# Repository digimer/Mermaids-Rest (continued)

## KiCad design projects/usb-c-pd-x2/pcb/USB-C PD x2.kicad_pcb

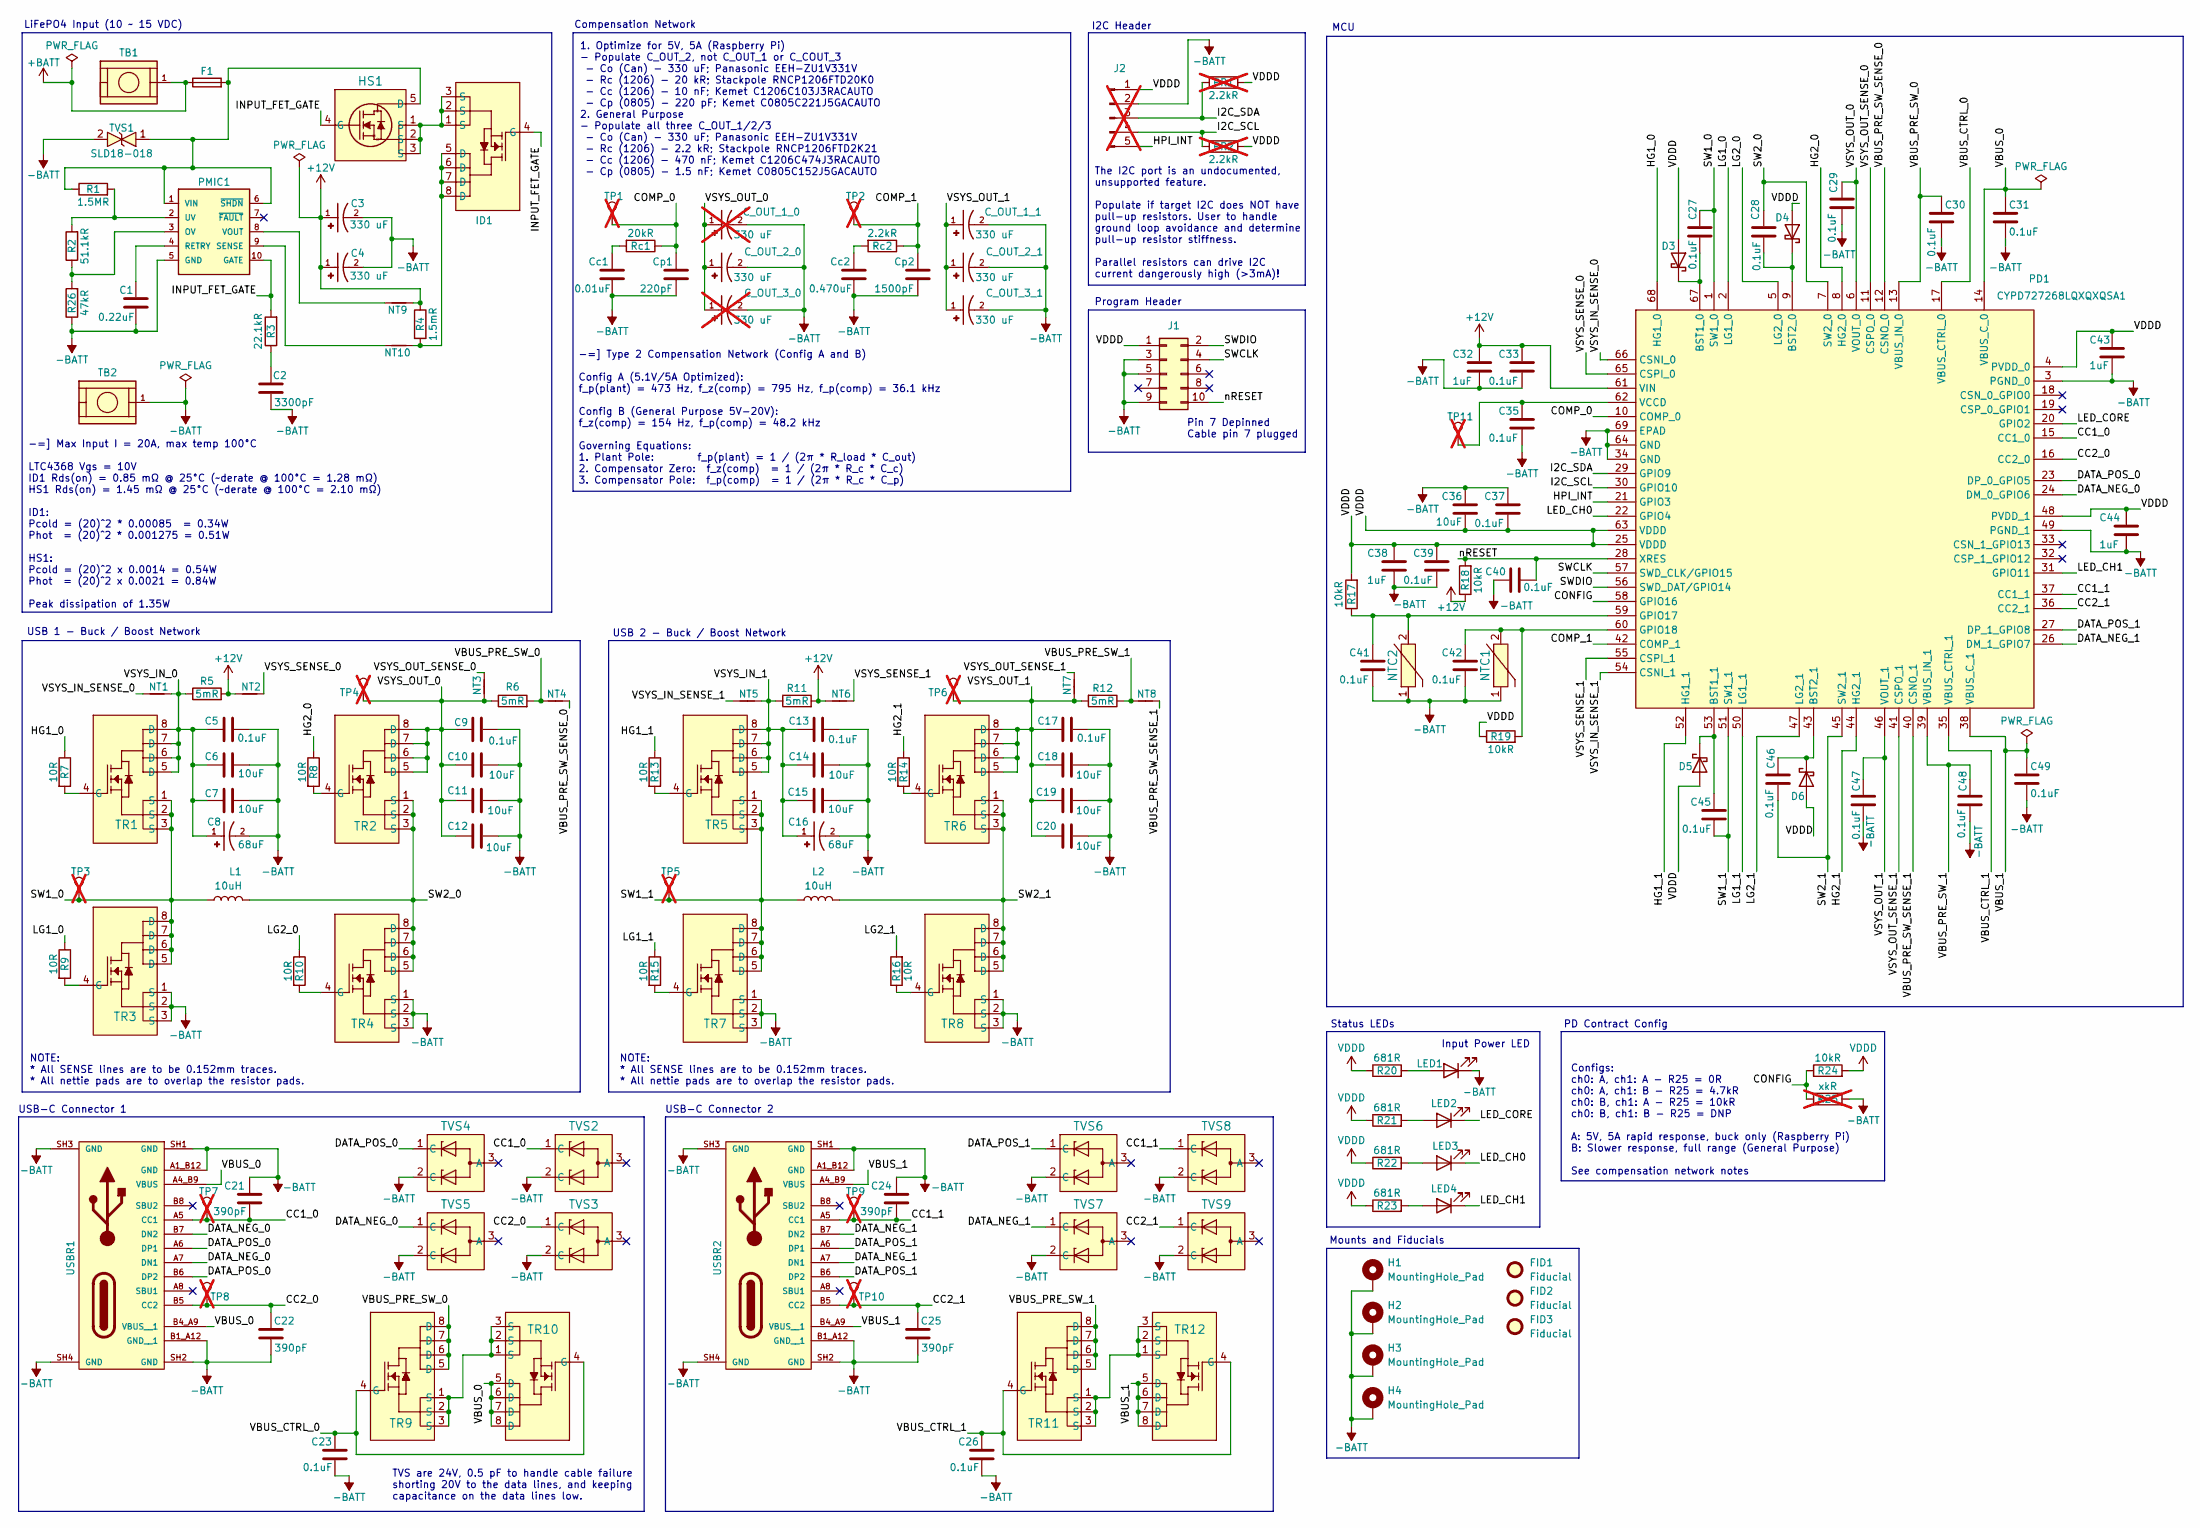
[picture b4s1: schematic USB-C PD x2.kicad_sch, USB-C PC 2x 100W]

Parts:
C1: 0.22uF; Kyocera AVX 08051A0R8CAT2A; Part Kyocera 08055C224J4Z2A
C2: 3300pF; C_0805_2012Metric; Part Kyocera KAM21BR71H332JT
C3, C4: 330 uF; Panasonic EEH-ZU; Part Panasonic EEH-ZU1V331V
C5, C9, C13, C17, C23, C26, C27, C28, C29, C30, C31, C33, C35, C37, C39, C40, C41, C42, C45, C46, C47, C48, C49: 0.1uF; Kyocera AVX 08051A0R8CAT2A; Part Kyocera 08051C104K4Z2A
C6, C7, C10, C11, C12, C14, C15, C18, C19, C20, C36: 10uF; TDK CGA5; Part TDK CGA5L1X7R1H106K160AE
C8, C16: 68uF; CP_Elec_8x10; Part Nichicon GXC1H680MCW1GS
C21, C22, C24, C25: 390pF; Yageo AC0805; Part Yageo AC0805JRNPO9BN391
C32, C38, C43, C44: 1uF; Kyocera AVX 08051A0R8CAT2A; Part Kyocera 08051C105K4Z2A
C_OUT_1_0, C_OUT_3_0: 330 uF; Panasonic EEH-ZU; Part Panasonic EEH-ZU1V331V; not fitted
C_OUT_1_1, C_OUT_2_0, C_OUT_2_1, C_OUT_3_1: 330 uF; Panasonic EEH-ZU; Part Panasonic EEH-ZU1V331V
Cc1: 0.01uF; C_1206_3216Metric; Part Kemet C1206C103J3RACAUTO
Cc2: 0.470uF; C_1206_3216Metric; Part Kemet C1206C474J3RACAUTO
Cp1: 220pF; C_0805_2012Metric; Part Kemet C0805C221J5GACAUTO
Cp2: 1500pF; C_0805_2012Metric; Part Kemet C0805C152J5GACAUTO
D3, D4, D5, D6: PMEG40T10ERX; Nexperia PMEG40; Part Nexperia PMEG40T10ERX
F1: Fuse; Littelfuse 178.6165.0001; Part Littelfuse 178.6165.0001
FID1, FID2, FID3: Fiducial; Fiducial_1mm_Mask2mm
H1, H2, H3, H4: MountingHole_Pad; MountingHole_4mm_Pad_Via
HS1: PSMN1R4-40YLDX; Nexperia PSMN1R4; Part Nexperia PSMN1R4-40YLDX
ID1: IAUC120N04S6L008ATMA1; Infineon IAUC120N04S6L008ATMA1; Part Infineon IAUC120N04S6L008ATMA1
J1: Conn_02x05_Odd_Even; PinHeader_2x05_P1.27mm_Vertical; Part Sullins GRPB052VWVN-RC
J2: Conn_01x05_Pin; PinHeader_1x05_P2.54mm_Vertical; Part Amphenol 68001-416HLF; not fitted
L1, L2: 10uH; Codaca CSBL1809-100M; Part Codaca CSBL1809-100M
LED1, LED2, LED3, LED4: LED; ams OSRAM LS Q976.01; Part ams OSRAM LS Q976.01-N1Q2-1
NT1, NT2, NT3, NT4, NT5, NT6, NT7, NT8, NT9, NT10: NetTie_2; NetTie-2_SMD_Pad0.2mm
NTC1, NTC2: Vishay NTCS0805E3103FHT; Vishay NTCS0805E; Part Vishay NTCS0805E3103FHT
PD1: CYPD727268LQXQXQSA1; QFN-68-1EP_8x8mm_P0.4mm_EP5.2x5.2mm_ThermalVias; Part Infineon CYPD727268LQXQXQSA1
PMIC1: ADI LTC4368; Part ADI LTC4368IMS-1#PBF
PR1, PR2: 2.2kR; R_1206_3216Metric; Part Stackpole RNCP1206FTD2K21; not fitted
R1: 1.5MR; Wurth WRIS-RSKS; Part Wurth 560112132040
R2: 51.1kR; R_1206_3216Metric; Part Stackpole RNCP1206FTD51K1
R3: 22.1kR; R_1206_3216Metric; Part Stackpole RNCP1206FTD22K1
R4: 1.5mR; Vishay WSLF2512; Part Vishay WSLF25121L500FEA
R5, R6, R11, R12: 5mR; Vishay WSLP; Part Vishay WSLP25125L000FEA
R7, R8, R9, R10, R13, R14, R15, R16: 10R; Stackpole RMCA0805; Part Stackpole RNCP0805FTD10R0
R17, R18, R19: 10kR; R_1206_3216Metric; Part Stackpole RNCP1206FTD10K0
R20, R21, R22, R23: 681R; Stackpole RMCA0805; Part Stackpole RNCP0805FTD681R
R24: 10kR; Stackpole_RNCP1206; Part Stackpole RNCP1206FTD10K0
R25: xkR; Stackpole_RNCP1206; Part See Config Note on Schematic; not fitted
R26: 47kR; R_1206_3216Metric; Part Stackpole RMCF1206FT47K0
Rc1: 20kR; R_1206_3216Metric; Part Stackpole RNCP1206FTD20K0
Rc2: 2.2kR; R_1206_3216Metric; Part Stackpole RNCP1206FTD2K21
TB1, TB2: 7799; Keystone 7799; Part Keystone 7799
TP1, TP2, TP3, TP4, TP5, TP6, TP7, TP8, TP9, TP10, TP11: TestPoint; PinHeader_1x01_P1.00mm_Vertical; Part Amphenol 68001-416HLF; not fitted
TR1, TR2, TR3, TR4, TR5, TR6, TR7, TR8, TR9, TR10, TR11, TR12: Diodes Inc DMTH45M5LPSWQ-13; Part Diodes Inc DMTH45M5LPSWQ-13
TVS1: SLD18-018; Littelfuse SDL; Part Littelfuse SLD18-018
TVS2, TVS3, TVS4, TVS5, TVS6, TVS7, TVS8, TVS9: MMBZ27VAL,215; Nexperia MMBZ27; Part Nexperia MMBZ27VAL,215
USBR1, USBR2: GCT USB4105-GF-A; Part GCT USB4105-GF-A

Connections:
+12V: C3.1, C4.1, C32.2, C33.1, NT2.1, NT6.1, NT9.1, PD1.61 (VIN), R4.1, R5.2, R11.2, R18.1
+BATT: F1.1, TB1.1
-BATT: C1.2, C2.2, C3.2, C4.2, C5.1, C6.1, C7.1, C8.2, C9.2, C10.2, C11.2, C12.2, C13.2, C14.2, C15.1, C16.2, C17.2, C18.2, C19.2, C20.2, C21.2, C22.1, C23.2, C24.2, C25.1, C26.2, C29.2, C30.2, C31.2, C32.1, C33.2, C35.2, C36.1, C37.1, C38.1, C39.2, C40.1, C41.2, C42.2, C43.1, C44.1, C47.2, C48.2, C49.2, C_OUT_1_0.2, C_OUT_1_1.2, C_OUT_2_0.2, C_OUT_2_1.2, C_OUT_3_0.2, C_OUT_3_1.2, Cc1.2, Cc2.2, Cp1.2, Cp2.2, H1.1 (1_1), H2.1 (1_1), H3.1 (1_1), H4.1 (1_1), J1.3, J1.5, J1.9, J2.2, LED1.1 (K), NTC1.1, NTC2.1, PD1.3 (PGND_0), PD1.34 (GND), PD1.49 (PGND_1), PD1.64 (GND), PD1.69 (EPAD), PMIC1.5 (GND), R25.2, R26.1, TB2.1, TR3.1 (S), TR3.2 (S), TR3.3 (S), TR4.1 (S), TR4.2 (S), TR4.3 (S), TR7.1 (S), TR7.2 (S), TR7.3 (S), TR8.1 (S), TR8.2 (S), TR8.3 (S), TVS1.2, TVS2.2 (C), TVS3.2 (C), TVS4.2 (C), TVS5.2 (C), TVS6.2 (C), TVS7.2 (C), TVS8.2 (C), TVS9.2 (C), USBR1.A1_B12 (GND), USBR1.B1_A12 (GND__1), USBR1.SH1 (GND), USBR1.SH2 (GND), USBR1.SH3 (GND), USBR1.SH4 (GND), USBR2.A1_B12 (GND), USBR2.B1_A12 (GND__1), USBR2.SH1 (GND), USBR2.SH2 (GND), USBR2.SH3 (GND), USBR2.SH4 (GND)
/CC1_0: C21.1, PD1.15 (CC1_0), TP7.1 (1_1), TVS2.1 (C), USBR1.A5 (CC1)
/CC1_1: C24.1, PD1.37 (CC1_1), TP9.1 (1_1), TVS8.1 (C), USBR2.A5 (CC1)
/CC2_0: C22.2, PD1.16 (CC2_0), TP8.1 (1_1), TVS3.1 (C), USBR1.B5 (CC2)
/CC2_1: C25.2, PD1.36 (CC2_1), TP10.1 (1_1), TVS9.1 (C), USBR2.B5 (CC2)
/COMP_0: Cp1.1, PD1.10 (COMP_0), Rc1.1, TP1.1 (1_1)
/COMP_1: Cp2.1, PD1.42 (COMP_1), Rc2.1, TP2.1 (1_1)
/CONFIG: PD1.58 (GPIO16), R24.1, R25.1
/DATA_NEG_0: PD1.24 (DM_0_GPIO6), TVS5.1 (C), USBR1.A7 (DN1), USBR1.B7 (DN2)
/DATA_NEG_1: PD1.26 (DM_1_GPIO7), TVS7.1 (C), USBR2.A7 (DN1), USBR2.B7 (DN2)
/DATA_POS_0: PD1.23 (DP_0_GPIO5), TVS4.1 (C), USBR1.A6 (DP1), USBR1.B6 (DP2)
/DATA_POS_1: PD1.27 (DP_1_GPIO8), TVS6.1 (C), USBR2.A6 (DP1), USBR2.B6 (DP2)
/HG1_0: PD1.68 (HG1_0), R7.1
/HG1_1: PD1.52 (HG1_1), R13.1
/HG2_0: PD1.8 (HG2_0), R8.1
/HG2_1: PD1.44 (HG2_1), R14.1
/HPI_INT: J2.5, PD1.21 (GPIO3)
/I2C_SCL: J2.4, PD1.30 (GPIO10), PR2.1
/I2C_SDA: J2.3, PD1.29 (GPIO9), PR1.1
/INPUT_FET_GATE: HS1.4 (G), ID1.4 (G), PMIC1.10 (GATE), R3.2
/LED_CH0: LED3.1 (K), PD1.22 (GPIO4)
/LED_CH1: LED4.1 (K), PD1.31 (GPIO11)
/LED_CORE: LED2.1 (K), PD1.20 (GPIO2)
/LG1_0: PD1.2 (LG1_0), R9.1
/LG1_1: PD1.50 (LG1_1), R15.1
/LG2_0: PD1.5 (LG2_0), R10.1
/LG2_1: PD1.47 (LG2_1), R16.2
/SW1_0: C27.1, L1.1, PD1.1 (SW1_0), TP3.1 (1_1), TR1.1 (S), TR1.2 (S), TR1.3 (S), TR3.5 (D), TR3.6 (D), TR3.7 (D), TR3.8 (D)
/SW1_1: C45.2, L2.1, PD1.51 (SW1_1), TP5.1 (1_1), TR5.1 (S), TR5.2 (S), TR5.3 (S), TR7.5 (D), TR7.6 (D), TR7.7 (D), TR7.8 (D)
/SW2_0: C28.1, L1.2, PD1.7 (SW2_0), TR2.1 (S), TR2.2 (S), TR2.3 (S), TR4.5 (D), TR4.6 (D), TR4.7 (D), TR4.8 (D)
/SW2_1: C46.2, L2.2, PD1.45 (SW2_1), TR6.1 (S), TR6.2 (S), TR6.3 (S), TR8.5 (D), TR8.6 (D), TR8.7 (D), TR8.8 (D)
/SWCLK: J1.4, PD1.57 (SWD_CLK/GPIO15)
/SWDIO: J1.2, PD1.56 (SWD_DAT/GPIO14)
/VBUS_0: C31.1, PD1.14 (VBUS_C_0), TR10.5 (D), TR10.6 (D), TR10.7 (D), TR10.8 (D), USBR1.A4_B9 (VBUS), USBR1.B4_A9 (VBUS__1)
/VBUS_1: C49.1, PD1.38 (VBUS_C_1), TR12.5 (D), TR12.6 (D), TR12.7 (D), TR12.8 (D), USBR2.A4_B9 (VBUS), USBR2.B4_A9 (VBUS__1)
/VBUS_CTRL_0: C23.1, PD1.17 (VBUS_CTRL_0), TR9.4 (G), TR10.4 (G)
/VBUS_CTRL_1: C26.1, PD1.35 (VBUS_CTRL_1), TR11.4 (G), TR12.4 (G)
/VBUS_PRE_SW_0: C30.1, NT4.1, PD1.13 (VBUS_IN_0), R6.2, TR9.5 (D), TR9.6 (D), TR9.7 (D), TR9.8 (D)
/VBUS_PRE_SW_1: C48.1, NT8.1, PD1.39 (VBUS_IN_1), R12.1, TR11.5 (D), TR11.6 (D), TR11.7 (D), TR11.8 (D)
/VBUS_PRE_SW_SENSE_0: NT4.2, PD1.12 (CSNO_0)
/VBUS_PRE_SW_SENSE_1: NT8.2, PD1.40 (CSNO_1)
/VSYS_IN_0: C5.2, C6.2, C7.2, C8.1, NT1.2, R5.1, TR1.5 (D), TR1.6 (D), TR1.7 (D), TR1.8 (D)
/VSYS_IN_1: C13.1, C14.1, C15.2, C16.1, NT5.2, R11.1, TR5.5 (D), TR5.6 (D), TR5.7 (D), TR5.8 (D)
/VSYS_IN_SENSE_0: NT1.1, PD1.66 (CSNI_0)
/VSYS_IN_SENSE_1: NT5.1, PD1.54 (CSNI_1)
/VSYS_OUT_0: C9.1, C10.1, C11.1, C12.1, C29.1, C_OUT_1_0.1, C_OUT_2_0.1, C_OUT_3_0.1, NT3.1, PD1.6 (VOUT_0), R6.1, TP4.1 (1_1), TR2.5 (D), TR2.6 (D), TR2.7 (D), TR2.8 (D)
/VSYS_OUT_1: C17.1, C18.1, C19.1, C20.1, C47.1, C_OUT_1_1.1, C_OUT_2_1.1, C_OUT_3_1.1, NT7.1, PD1.46 (VOUT_1), R12.2, TP6.1 (1_1), TR6.5 (D), TR6.6 (D), TR6.7 (D), TR6.8 (D)
/VSYS_OUT_SENSE_0: NT3.2, PD1.11 (CSPO_0)
/VSYS_OUT_SENSE_1: NT7.2, PD1.41 (CSPO_1)
/VSYS_SENSE_0: NT2.2, PD1.65 (CSPI_0)
/VSYS_SENSE_1: NT6.2, PD1.55 (CSPI_1)
/nRESET: C40.2, J1.10, PD1.28 (XRES), R18.2
unnamed: C2.1, R3.1
unnamed: Cc1.1, Rc1.2
unnamed: Cc2.1, Rc2.2
unnamed: C27.2, D3.1 (K), PD1.67 (BST1_0)
unnamed: C28.2, D4.1 (K), PD1.9 (BST2_0)
unnamed: C45.1, D5.1 (K), PD1.53 (BST1_1)
unnamed: C46.1, D6.1 (K), PD1.43 (BST2_1)
unnamed: F1.2, HS1.5 (D), PMIC1.1 (VIN), PMIC1.6 (~SHDN), R1.1, TVS1.1
unnamed: HS1.1 (S), HS1.2 (S), HS1.3 (S), ID1.1 (S), ID1.2 (S), ID1.3 (S)
unnamed: ID1.5 (D), ID1.6 (D), ID1.7 (D), ID1.8 (D), NT10.1, R4.2
unnamed: LED1.2 (A), R20.2
unnamed: LED2.2 (A), R21.2
unnamed: LED3.2 (A), R22.2
unnamed: LED4.2 (A), R23.2
unnamed: C41.1, NTC2.2, PD1.59 (GPIO17), R17.1
unnamed: C42.1, NTC1.2, PD1.60 (GPIO18), R19.2
unnamed: C35.1, PD1.62 (VCCD), TP11.1 (1_1)
unnamed: PMIC1.3 (OV), R2.1, R26.2
unnamed: C1.1, PMIC1.4 (RETRY)
unnamed: NT10.2, PMIC1.9 (SENSE)
unnamed: PMIC1.2 (UV), R1.2, R2.2
unnamed: NT9.2, PMIC1.8 (VOUT)
unnamed: R7.2, TR1.4 (G)
unnamed: R8.2, TR2.4 (G)
unnamed: R9.2, TR3.4 (G)
unnamed: R10.2, TR4.4 (G)
unnamed: R13.2, TR5.4 (G)
unnamed: R14.2, TR6.4 (G)
unnamed: R15.2, TR7.4 (G)
unnamed: R16.1, TR8.4 (G)
unnamed: TR9.1 (S), TR9.2 (S), TR9.3 (S), TR10.1 (S), TR10.2 (S), TR10.3 (S)
unnamed: TR11.1 (S), TR11.2 (S), TR11.3 (S), TR12.1 (S), TR12.2 (S), TR12.3 (S)
VDDD: C36.2, C37.2, C38.2, C39.1, C43.2, C44.2, D3.2 (A), D4.2 (A), D5.2 (A), D6.2 (A), J1.1, J2.1, PD1.4 (PVDD_0), PD1.25 (VDDD), PD1.48 (PVDD_1), PD1.63 (VDDD), PR1.2, PR2.2, R17.2, R19.1, R20.1, R21.1, R22.1, R23.1, R24.2

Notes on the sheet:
LiFePO4 Input (10 ~ 15 VDC)
MCU
1. Optimize for 5V, 5A (Raspberry Pi) - Populate C_OUT_2, not C_OUT_1 or C_COUT_3 - Co (Can) - 330 uF; Panasonic EEH-ZU1V331V - Rc (1206) - 20 kR; Stackpole RNCP1206FTD20K0 - Cc (1206) - 10 nF; Kemet C1206C103J3RACAUTO - Cp (0805) - 220 pF; Kemet C0805C221J5GACAUTO 2. General Purpose - Populate all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
Input Power LED
Mounts and Fiducials
NOTE: * All SENSE lines are to be 0.152mm traces. * All nettie pads are to overlap the resistor pads.
-=] Type 2 Compensation Network (Config A and B) Config A (5.1V/5A Optimized): f_p(plant) = 473 Hz, f_z(comp) = 795 Hz, f_p(comp) = 36.1 kHz Config B (General Purpose 5V-20V): f_z(comp) = 154 Hz, f_p(comp) = 48.2 kHz Governing Equations: 1. Plant Pole: f_p(plant) = 1 / (2π * R_load * C_out) 2. Comp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
Status LEDs
TVS are 24V, 0.5 pF to handle cable failure shorting 20V to the data lines, and keeping capacitance on the data lines low.
I2C Header
PD Contract Config
-=] Max Input I = 20A, max temp 100°C LTC4368 Vgs = 10V ID1 Rds(on) = 0.85 mΩ @ 25°C (~derate @ 100°C = 1.28 mΩ) HS1 Rds(on) = 1.45 mΩ @ 25°C (~derate @ 100°C = 2.10 mΩ) ID1: Pcold = (20)^2 * 0.00085 = 0.34W Phot = (20)^2 * 0.001275 = 0.51W HS1: Pcold = (20)^2 x 0.0014 = 0.54W Phot = (20)^2 x 0.002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
USB 1 - Buck / Boost Network
Configs: ch0: A, ch1: A - R25 = 0R ch0: A, ch1: B - R25 = 4.7kR ch0: B, ch1: A - R25 = 10kR ch0: B, ch1: B - R25 = DNP A: 5V, 5A rapid response, buck only (Raspberry Pi) B: Slower response, full range (General Purpose) See compensation network notes
USB-C Connector 1
USB 2 - Buck / Boost Network
USB-C Connector 2
Program Header
Pin 7 Depinned Cable pin 7 plugged
The I2C port is an undocumented, unsupported feature. Populate if target I2C does NOT have pull-up resistors. User to handle ground loop avoidance and determine pull-up resistor stiffness. Parallel resistors can drive I2C current dangerously high (>3mA)!
Compensation Network

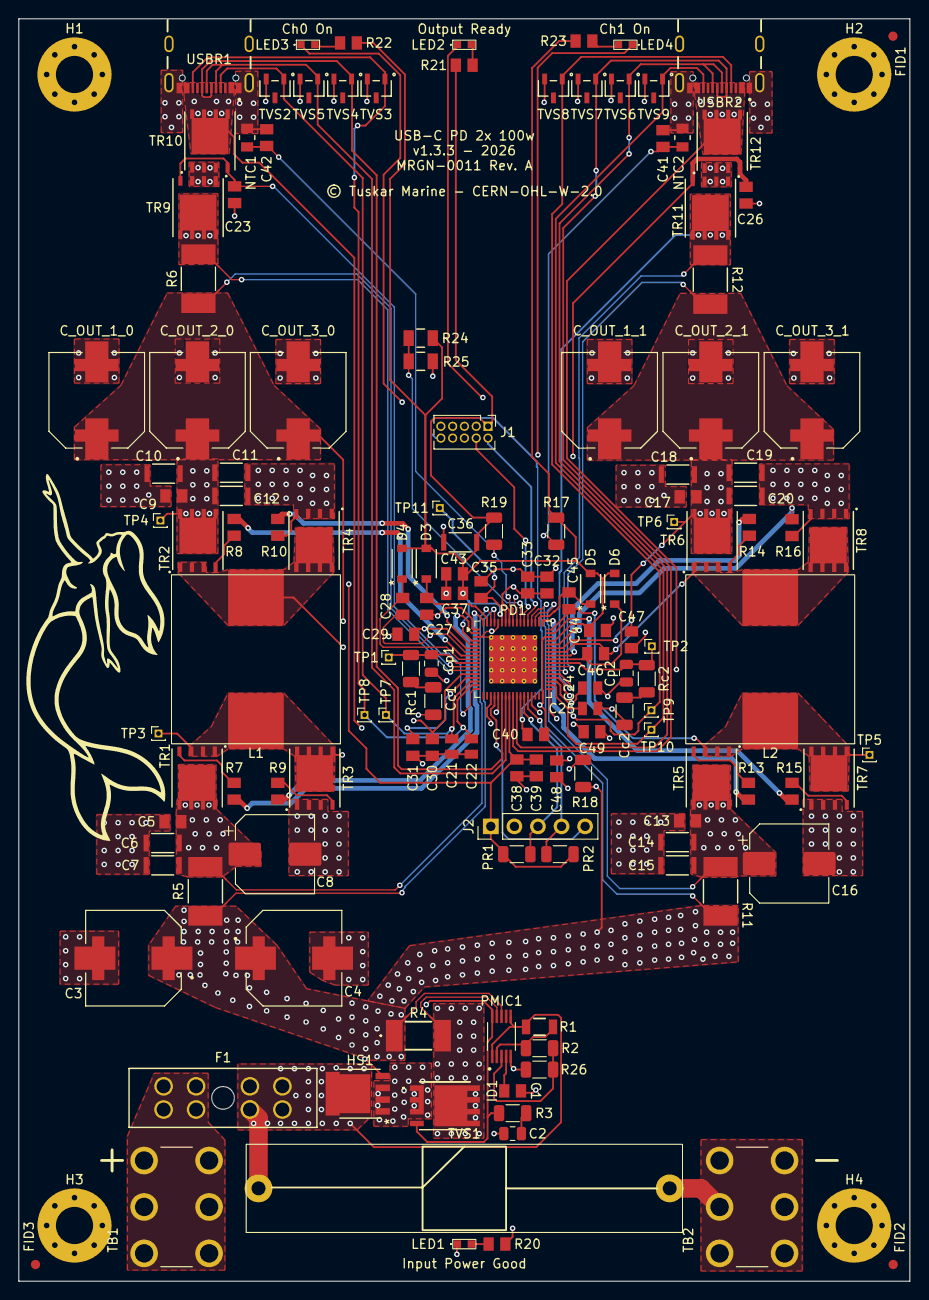
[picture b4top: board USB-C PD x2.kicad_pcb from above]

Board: 4 copper layers, 96.0 x 136.0 mm, 160 parts (0 on the bottom side), 87 nets.

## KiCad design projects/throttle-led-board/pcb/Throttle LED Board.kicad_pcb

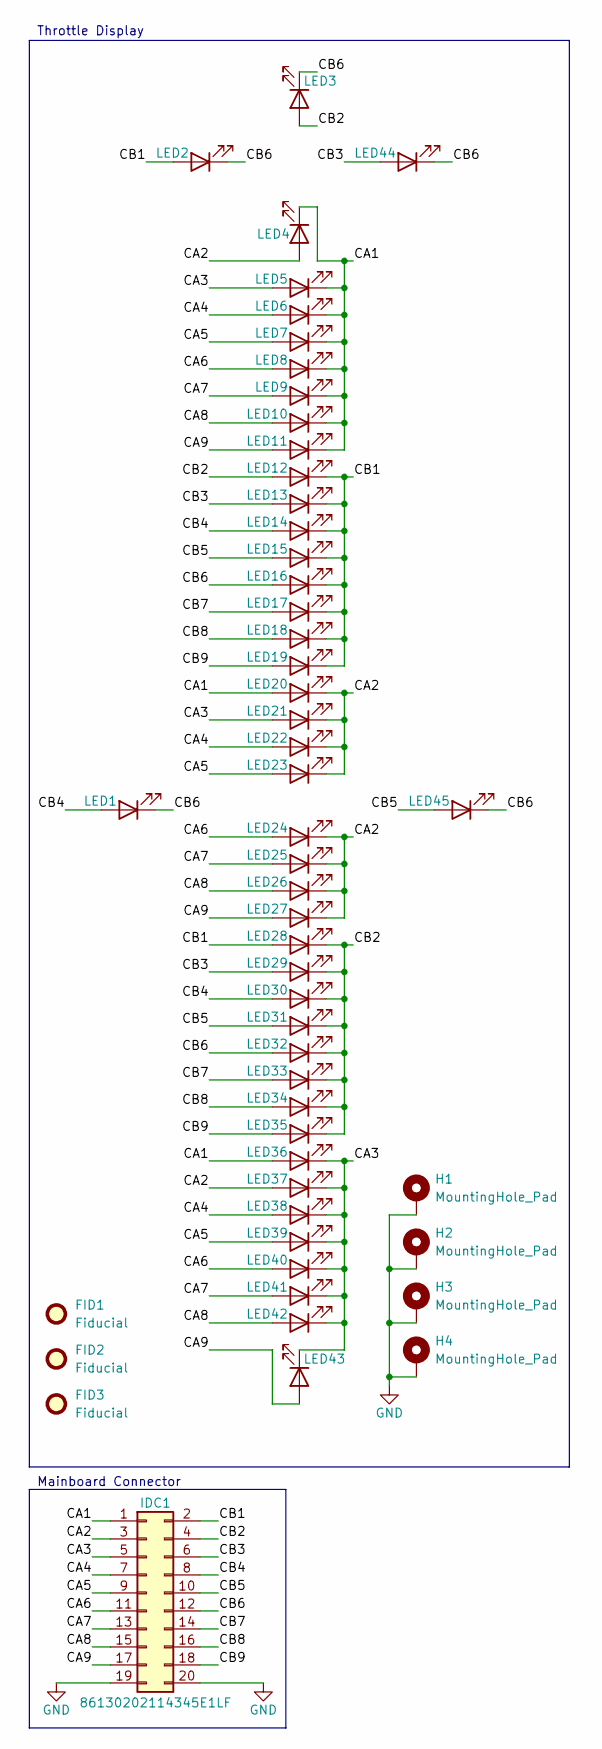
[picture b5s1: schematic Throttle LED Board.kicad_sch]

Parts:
FID1, FID2, FID3: Fiducial; Fiducial_0.5mm_Mask1mm
H1, H2, H3, H4: MountingHole_Pad; MountingHole_4mm_Pad_Via
IDC1: 86130202114345E1LF; Amphenol 86130202114345E1LF; Part Amphenol 86130202114345E1LF
LED1, LED2, LED3, LED4, LED5, LED6, LED7, LED8, LED9, LED10, LED11, LED12, LED13, LED14, LED15, LED16, LED17, LED18, LED19, LED20, LED21, LED22, LED23, LED24, LED25, LED26, LED27, LED28, LED29, LED30, LED31, LED32, LED33, LED34, LED35, LED36, LED37, LED38, LED39, LED40, LED41, LED42, LED43, LED44, LED45: LED; Kingbright WP383SURDTK; Part Kingbright WP383SURDTK

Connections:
/CA1: IDC1.1, LED4.1 (K), LED5.1 (K), LED6.1 (K), LED7.1 (K), LED8.1 (K), LED9.1 (K), LED10.1 (K), LED11.1 (K), LED20.2 (A), LED36.2 (A)
/CA2: IDC1.3, LED4.2 (A), LED20.1 (K), LED21.1 (K), LED22.1 (K), LED23.1 (K), LED24.1 (K), LED25.1 (K), LED26.1 (K), LED27.1 (K), LED37.2 (A)
/CA3: IDC1.5, LED5.2 (A), LED21.2 (A), LED36.1 (K), LED37.1 (K), LED38.1 (K), LED39.1 (K), LED40.1 (K), LED41.1 (K), LED42.1 (K), LED43.1 (K)
/CA4: IDC1.7, LED6.2 (A), LED22.2 (A), LED38.2 (A)
/CA5: IDC1.9, LED7.2 (A), LED23.2 (A), LED39.2 (A)
/CA6: IDC1.11, LED8.2 (A), LED24.2 (A), LED40.2 (A)
/CA7: IDC1.13, LED9.2 (A), LED25.2 (A), LED41.2 (A)
/CA8: IDC1.15, LED10.2 (A), LED26.2 (A), LED42.2 (A)
/CA9: IDC1.17, LED11.2 (A), LED27.2 (A), LED43.2 (A)
/CB1: IDC1.2, LED2.2 (A), LED12.1 (K), LED13.1 (K), LED14.1 (K), LED15.1 (K), LED16.1 (K), LED17.1 (K), LED18.1 (K), LED19.1 (K), LED28.2 (A)
/CB2: IDC1.4, LED3.2 (A), LED12.2 (A), LED28.1 (K), LED29.1 (K), LED30.1 (K), LED31.1 (K), LED32.1 (K), LED33.1 (K), LED34.1 (K), LED35.1 (K)
/CB3: IDC1.6, LED13.2 (A), LED29.2 (A), LED44.2 (A)
/CB4: IDC1.8, LED1.2 (A), LED14.2 (A), LED30.2 (A)
/CB5: IDC1.10, LED15.2 (A), LED31.2 (A), LED45.2 (A)
/CB6: IDC1.12, LED1.1 (K), LED2.1 (K), LED3.1 (K), LED16.2 (A), LED32.2 (A), LED44.1 (K), LED45.1 (K)
/CB7: IDC1.14, LED17.2 (A), LED33.2 (A)
/CB8: IDC1.16, LED18.2 (A), LED34.2 (A)
/CB9: IDC1.18, LED19.2 (A), LED35.2 (A)
GND: H1.1 (1_1), H2.1 (1_1), H3.1 (1_1), H4.1 (1_1), IDC1.19, IDC1.20

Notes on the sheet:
Throttle Display
Mainboard Connector

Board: 4 copper layers, 53 parts (1 on the bottom side), 19 nets, no tracks yet.

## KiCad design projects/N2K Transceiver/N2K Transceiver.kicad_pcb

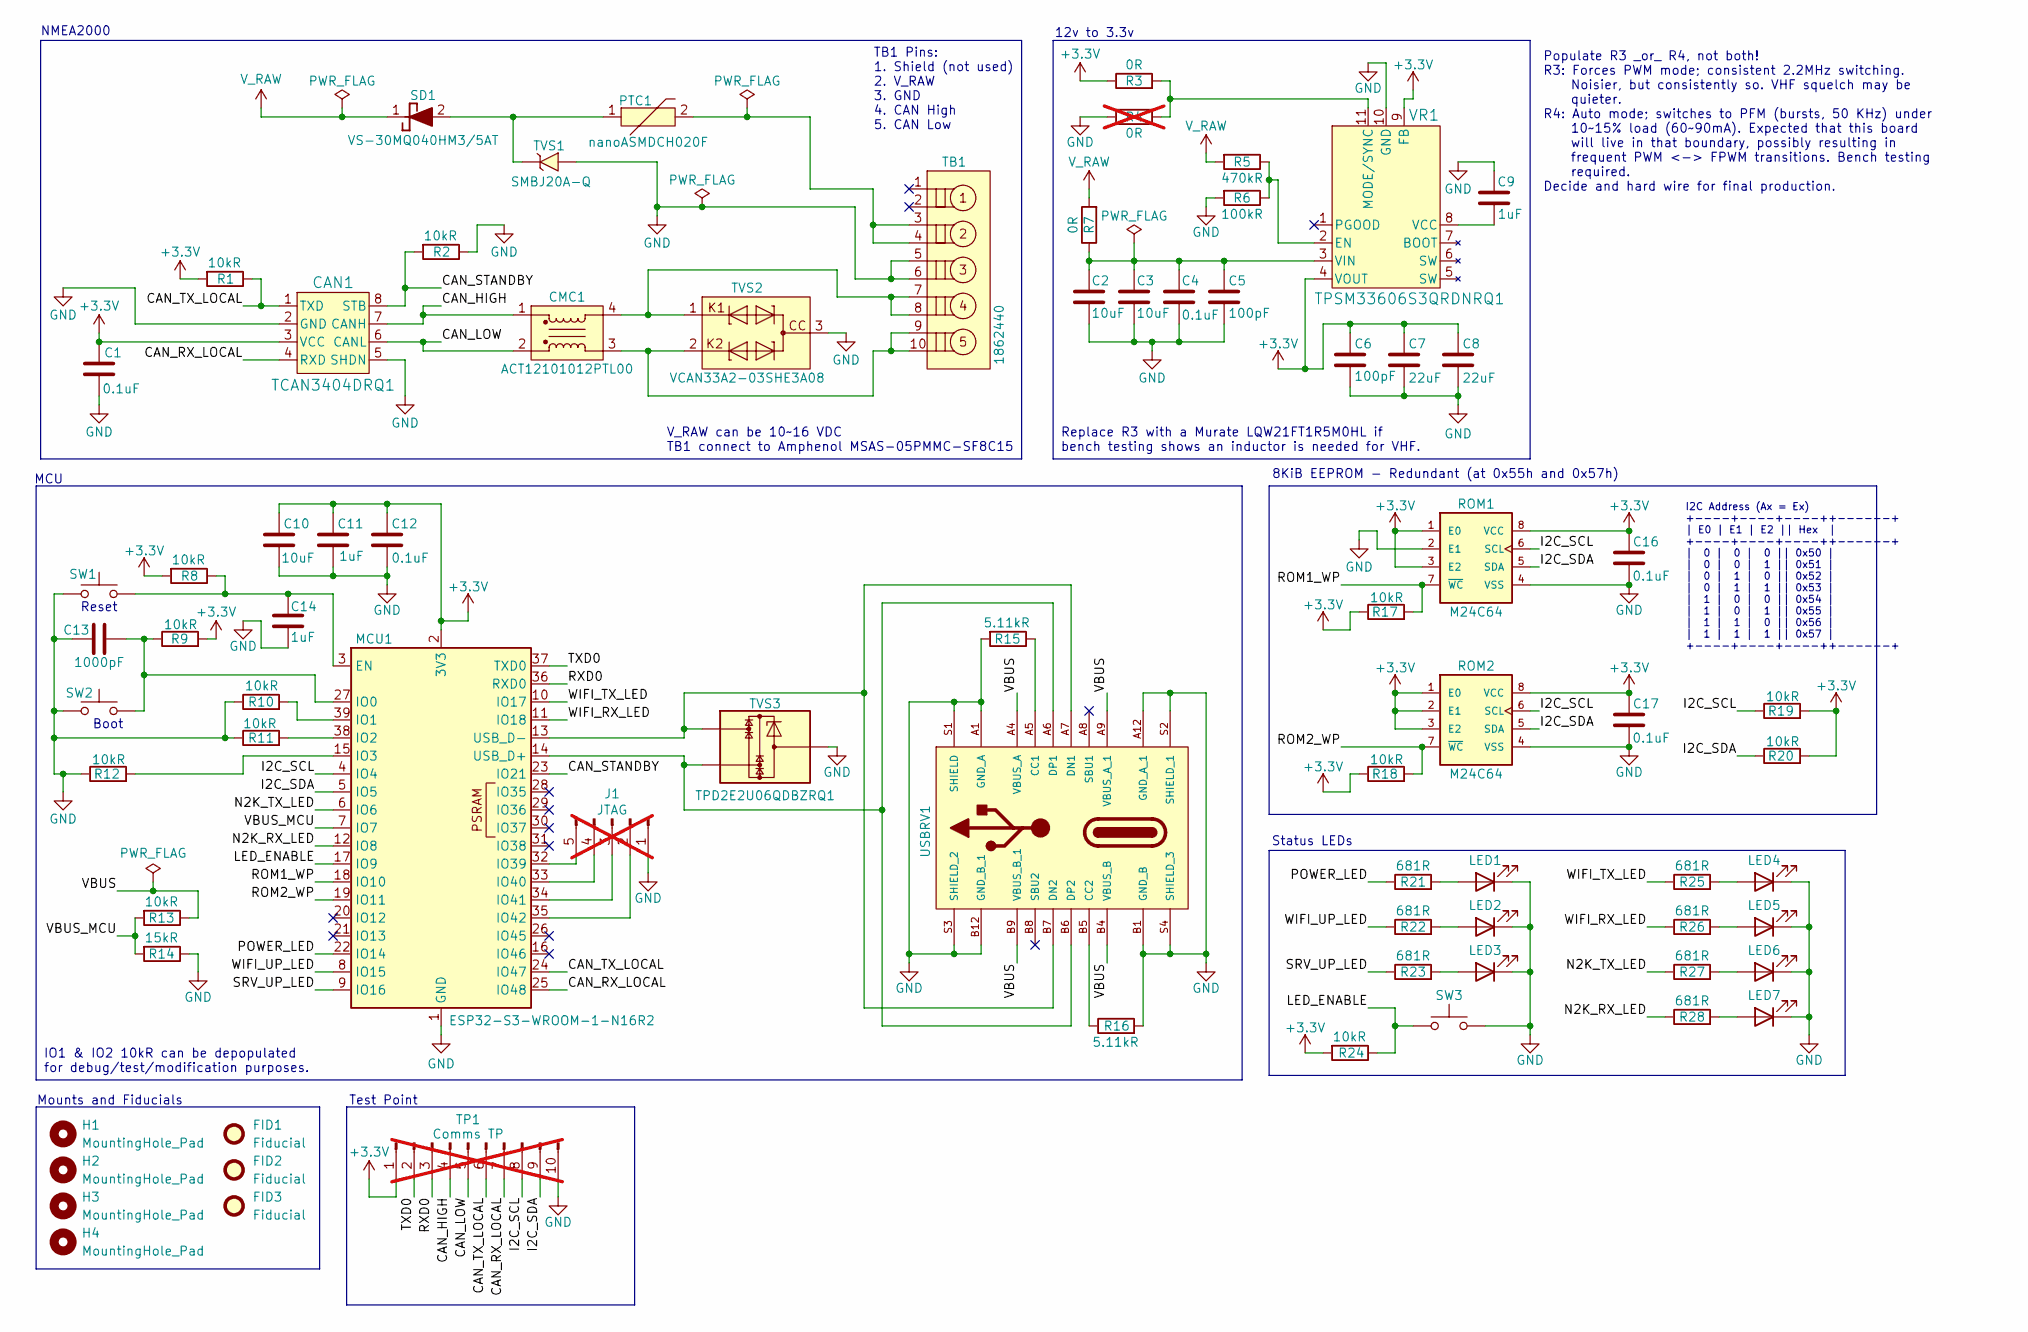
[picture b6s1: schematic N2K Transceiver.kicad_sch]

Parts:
C1, C4, C12, C16, C17: 0.1uF; Kyocera AVX 0805; Part Kyocera 08051C104K4Z2A
C2, C3, C10: 10uF; TDK CGA5; Part TDK CGA5L1X7R1H106K160AE
C5, C6: 100pF; Kemet C0805X; Part Kemet C0805X101J5GACAUTO
C7, C8: 22uF; Murata GCJ32ER71C; Part Murata GCJ32ER71C226KE01L
C9, C11, C14: 1uF; Kyocera AVX 0805; Part Kyocera 08051C105K4Z2A
C13: 1000pF; TDK CGA 0805; Part TDK CGA4F2X7R2A102K085AE
CAN1: TCAN3404DRQ1; TI TCAN3404; Part TI TCAN3404DRQ1
CMC1: ACT12101012PTL00; TDK ACT12101012PTL00; Part TDK ACT1210-101-2P-TL00
FID1, FID2, FID3: Fiducial; Fiducial_1mm_Mask2mm
H1, H2, H3, H4: MountingHole_Pad; MountingHole_4.3mm_M4
J1: JTAG; PinHeader_1x05_P2.54mm_Vertical; not fitted
LED1, LED2, LED3, LED4, LED5, LED6, LED7: LED; ams OSRAM LS Q976.01; Part ams OSRAM LS Q976.01-N1Q2-1
MCU1: ESP32-S3-WROOM-1-N16R2; ESP32-S3-WROOM-1; Part Espressif ESP32-S3-WROOM-1-N16R2
PTC1: nanoASMDCH020F; Littelfuse NANOASMDCH020F; Part Littelfuse nanoASMDCH020F
R1, R2, R8, R9, R10, R11, R12, R13, R17, R18, R19, R20, R24: 10kR; Stackpole_RNCP1206; Part Stackpole RNCP1206FTD10K0
R3, R7: 0R; Vishay RCA-SR e3; Part Vishay RCA08050000ZSEASR
R4: 0R; Vishay RCA-SR e3; Part Vishay RCA08050000ZSEASR; not fitted
R5: 470kR; Wurth WRIS-RSKS; Part Wurth 560112120009
R6: 100kR; Stackpole RMCA0805; Part Stackpole RMCA0805FT100K-HP
R14: 15kR; Stackpole_RNCP1206; Part Stackpole RNCP1206FTD15K0
R15, R16: 5.11kR; Stackpole_RNCP1206; Part Stackpole RNCP1206FTD5K11
R21, R22, R23, R25, R26, R27, R28: 681R; Stackpole RMCA0805; Part Stackpole RNCP0805FTD681R
ROM1, ROM2: M24C64; STM M24C64-RMN6P; Part STM M24C64-RMN6P
SD1: VS-30MQ040HM3/5AT; Vishay 30MQ040; Part Vishay VS-30MQ040-M3_5AT
SW1, SW2, SW3: SW_MEC_5G; SW_TS03-66-50-BK-160-LCR-D-67; Part Same Sky TS03-66-50-BK-160-LCR-D-67
TB1: 1862440; Phoenix Contact 1862440; Part Phoenix Contact 1862440
TP1: Comms TP; PinHeader_1x10_P2.54mm_Vertical; not fitted
TVS1: SMBJ20A-Q; Bourns SMBJ20; Part Bourns SMBJ20A-Q
TVS2: VCAN33A2-03SHE3A08; Vishay VCAN33A2-03S; Part Vishay VCAN33A2-03SHE3A08
TVS3: TPD2E2U06QDBZRQ1; TI TPD2E2U06; Part TI TPD2E2U06QDBZRQ1
USBRV1: USB4145-03-0170-C; GCT USB4145-03-0170-C; Part GCT USB4145-03-0170-C
VR1: TPSM33606S3QRDNRQ1; TI TPSM336; Part TI TPSM33606S3QRDNRQ1

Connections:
+3.3V: C1.2, C6.1, C7.1, C8.1, C10.2, C11.1, C12.1, C16.2, C17.2, CAN1.3 (VCC), MCU1.2 (3V3), R1.2, R3.1, R8.2, R9.2, R17.1, R18.1, R19.2, R20.2, R24.2, ROM1.1 (E0), ROM1.3 (E2), ROM1.8 (VCC), ROM2.1 (E0), ROM2.2 (E1), ROM2.3 (E2), ROM2.8 (VCC), TP1.1, VR1.4 (VOUT), VR1.9 (FB)
/CAN_HIGH: CAN1.7 (CANH), CMC1.1 (I1), TP1.4
/CAN_LOW: CAN1.6 (CANL), CMC1.2 (I2), TP1.5
/CAN_RX_LOCAL: CAN1.4 (RXD), MCU1.25 (IO48), TP1.7
/CAN_STANDBY: CAN1.8 (STB), MCU1.23 (IO21), R2.2
/CAN_TX_LOCAL: CAN1.1 (TXD), MCU1.24 (IO47), R1.1, TP1.6
/I2C_SCL: MCU1.4 (IO4), R19.1, ROM1.6 (SCL), ROM2.6 (SCL), TP1.8
/I2C_SDA: MCU1.5 (IO5), R20.1, ROM1.5 (SDA), ROM2.5 (SDA), TP1.9
/LED_ENABLE: MCU1.17 (IO9), R24.1, SW3.1 (A), SW3.2 (A)
/N2K_RX_LED: MCU1.12 (IO8), R28.1
/N2K_TX_LED: MCU1.6 (IO6), R27.1
/POWER_LED: MCU1.22 (IO14), R21.1
/ROM1_WP: MCU1.18 (IO10), R17.2, ROM1.7 (~WC)
/ROM2_WP: MCU1.19 (IO11), R18.2, ROM2.7 (~WC)
/RXD0: MCU1.36 (RXD0), TP1.3
/SRV_UP_LED: MCU1.9 (IO16), R23.1
/TXD0: MCU1.37 (TXD0), TP1.2
/VBUS: R13.1, USBRV1.A4 (VBUS_A), USBRV1.A9 (VBUS_A_1), USBRV1.B4 (VBUS_B), USBRV1.B9 (VBUS_B_1)
/VBUS_MCU: MCU1.7 (IO7), R13.2, R14.2
/WIFI_RX_LED: MCU1.11 (IO18), R26.1
/WIFI_TX_LED: MCU1.10 (IO17), R25.1
/WIFI_UP_LED: MCU1.8 (IO15), R22.1
GND: C1.1, C2.2, C3.2, C4.2, C5.2, C6.2, C7.2, C8.2, C9.2, C10.1, C11.2, C12.2, C13.1, C14.2, C16.1, C17.1, CAN1.2 (GND), CAN1.5 (SHDN), J1.1, LED1.1 (K), LED2.1 (K), LED3.1 (K), LED4.1 (K), LED5.1 (K), LED6.1 (K), LED7.1 (K), MCU1.1 (GND), MCU1.40 (GND), MCU1.41 (GND), R2.1, R4.2, R6.2, R10.1, R11.1, R12.1, R14.1, R15.2, R16.2, ROM1.2 (E1), ROM1.4 (VSS), ROM2.4 (VSS), SW1.1 (A), SW1.2 (A), SW2.1 (A), SW2.2 (A), SW3.3 (B), SW3.4 (B), TB1.5, TB1.6, TP1.10, TVS1.2 (A), TVS2.3, TVS3.3 (GND), USBRV1.A1 (GND_A), USBRV1.A12 (GND_A_1), USBRV1.B1 (GND_B), USBRV1.B12 (GND_B_1), USBRV1.S1 (SHIELD), USBRV1.S2 (SHIELD_1), USBRV1.S3 (SHIELD_2), USBRV1.S4 (SHIELD_3), VR1.10 (GND)
unnamed: CMC1.4 (O1), TB1.7, TB1.8, TVS2.1
unnamed: CMC1.3 (O2), TB1.9, TB1.10, TVS2.2
unnamed: J1.2, MCU1.35 (IO42)
unnamed: J1.3, MCU1.34 (IO41)
unnamed: J1.4, MCU1.33 (IO40)
unnamed: J1.5, MCU1.32 (IO39)
unnamed: LED1.2 (A), R21.2
unnamed: LED2.2 (A), R22.2
unnamed: LED3.2 (A), R23.2
unnamed: LED4.2 (A), R25.2
unnamed: LED5.2 (A), R26.2
unnamed: LED6.2 (A), R27.2
unnamed: LED7.2 (A), R28.2
unnamed: C14.1, MCU1.3 (EN), R8.1, SW1.3 (B), SW1.4 (B)
unnamed: C13.2, MCU1.27 (IO0), R9.1, SW2.3 (B), SW2.4 (B)
unnamed: MCU1.39 (IO1), R10.2
unnamed: MCU1.38 (IO2), R11.2
unnamed: MCU1.15 (IO3), R12.2
unnamed: MCU1.14 (USB_D+), TVS3.2 (IO2), USBRV1.A6 (DP1), USBRV1.B6 (DP2)
unnamed: MCU1.13 (USB_D-), TVS3.1 (IO1), USBRV1.A7 (DN1), USBRV1.B7 (DN2)
unnamed: PTC1.2, TB1.3, TB1.4
unnamed: PTC1.1, SD1.2 (A), TVS1.1 (K)
unnamed: R15.1, USBRV1.A5 (CC1)
unnamed: R16.1, USBRV1.B5 (CC2)
unnamed: R5.1, R6.1, VR1.2 (EN)
unnamed: R3.2, R4.1, VR1.11 (MODE/SYNC)
unnamed: C9.1, VR1.8 (VCC)
unnamed: C2.1, C3.1, C4.1, C5.1, R7.1, VR1.3 (VIN)
V_RAW: R5.2, R7.2, SD1.1 (K)

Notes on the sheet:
V_RAW can be 10~16 VDC TB1 connect to Amphenol MSAS-05PMMC-SF8C15
MCU
Mounts and Fiducials
Test Point
Replace R3 with a Murate LQW21FT1R5M0HL if bench testing shows an inductor is needed for VHF.
Boot
Status LEDs
IO1 & IO2 10kR can be depopulated for debug/test/modification purposes.
NMEA2000
I2C Address (Ax = Ex) +----+----+----++------+ | E0 | E1 | E2 || Hex | +----+----+----++------+ | 0 | 0 | 0 || 0x50 | | 0 | 0 | 1 || 0x51 | | 0 | 1 | 0 || 0x52 | | 0 | 1 | 1 || 0x53 | | 1 | 0 | 0 || 0x54 | | 1 | 0 | 1 || 0x55 | | 1 | 1 | 0 || 0x56 | | 1 | 1 | 1 || 0x57 | +----+----+----++------+
Reset
Populate R3 _or_ R4, not both! R3: Forces PWM mode; consistent 2.2MHz switching. Noisier, but consistently so. VHF squelch may be quieter. R4: Auto mode; switches to PFM (bursts, 50 KHz) under 10~15% load (60~90mA). Expected that this board will live in that boundary, possibly resulting in frequent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
TB1 Pins: 1. Shield (not used) 2. V_RAW 3. GND 4. CAN High 5. CAN Low
12v to 3.3v
8KiB EEPROM - Redundant (at 0x55h and 0x57h)

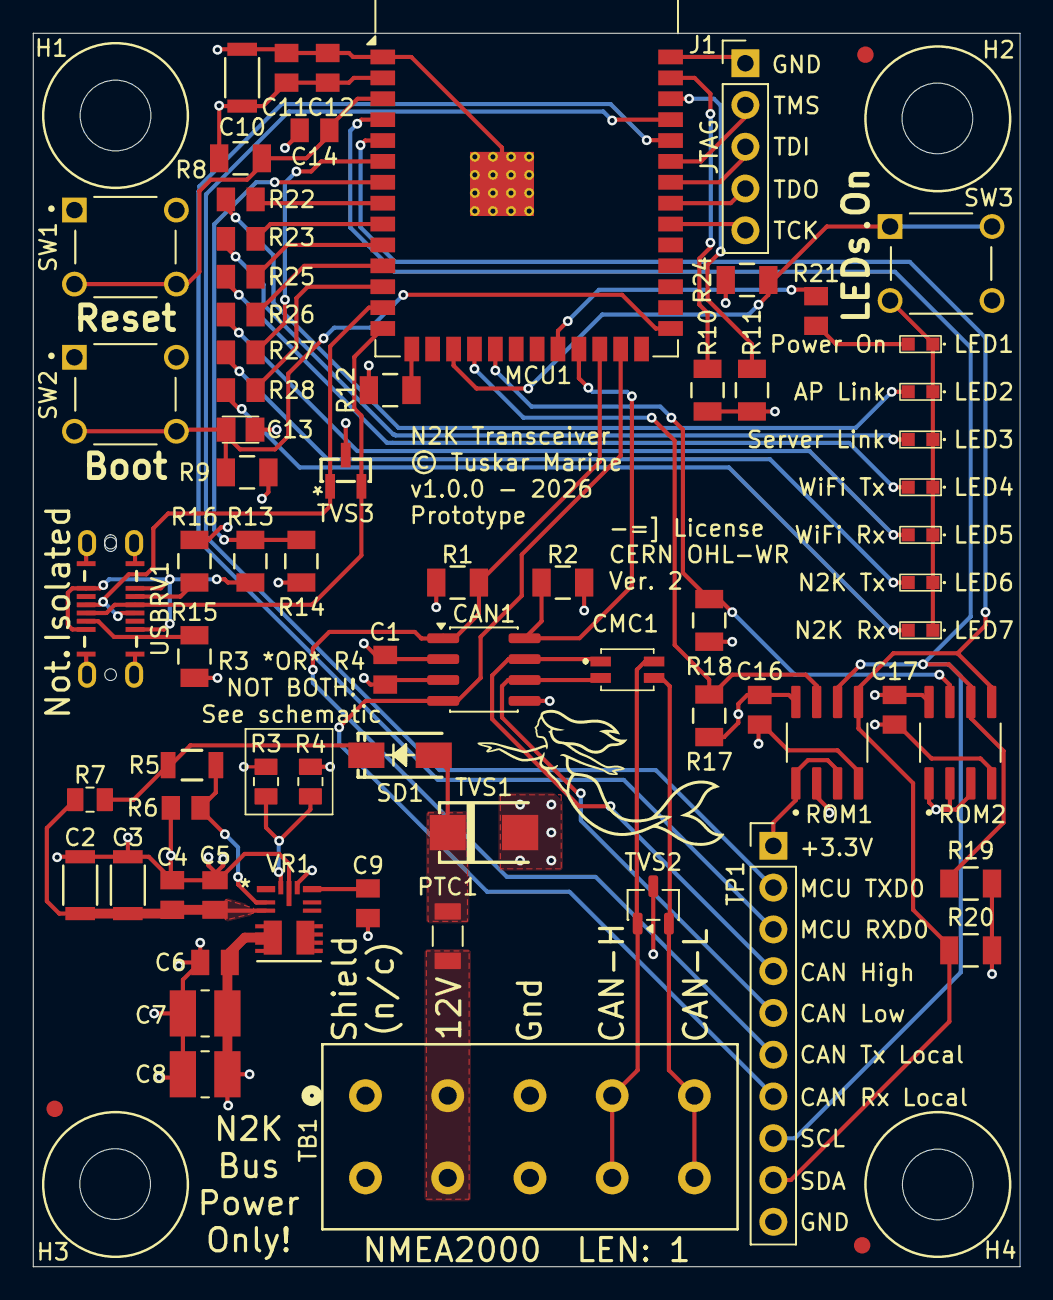
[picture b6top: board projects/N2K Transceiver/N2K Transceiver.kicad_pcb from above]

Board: 4 copper layers, 60.0 x 75.0 mm, 76 parts (0 on the bottom side), 52 nets.
